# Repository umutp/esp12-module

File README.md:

# esp12-module
Simple Esp12 module design for home automation

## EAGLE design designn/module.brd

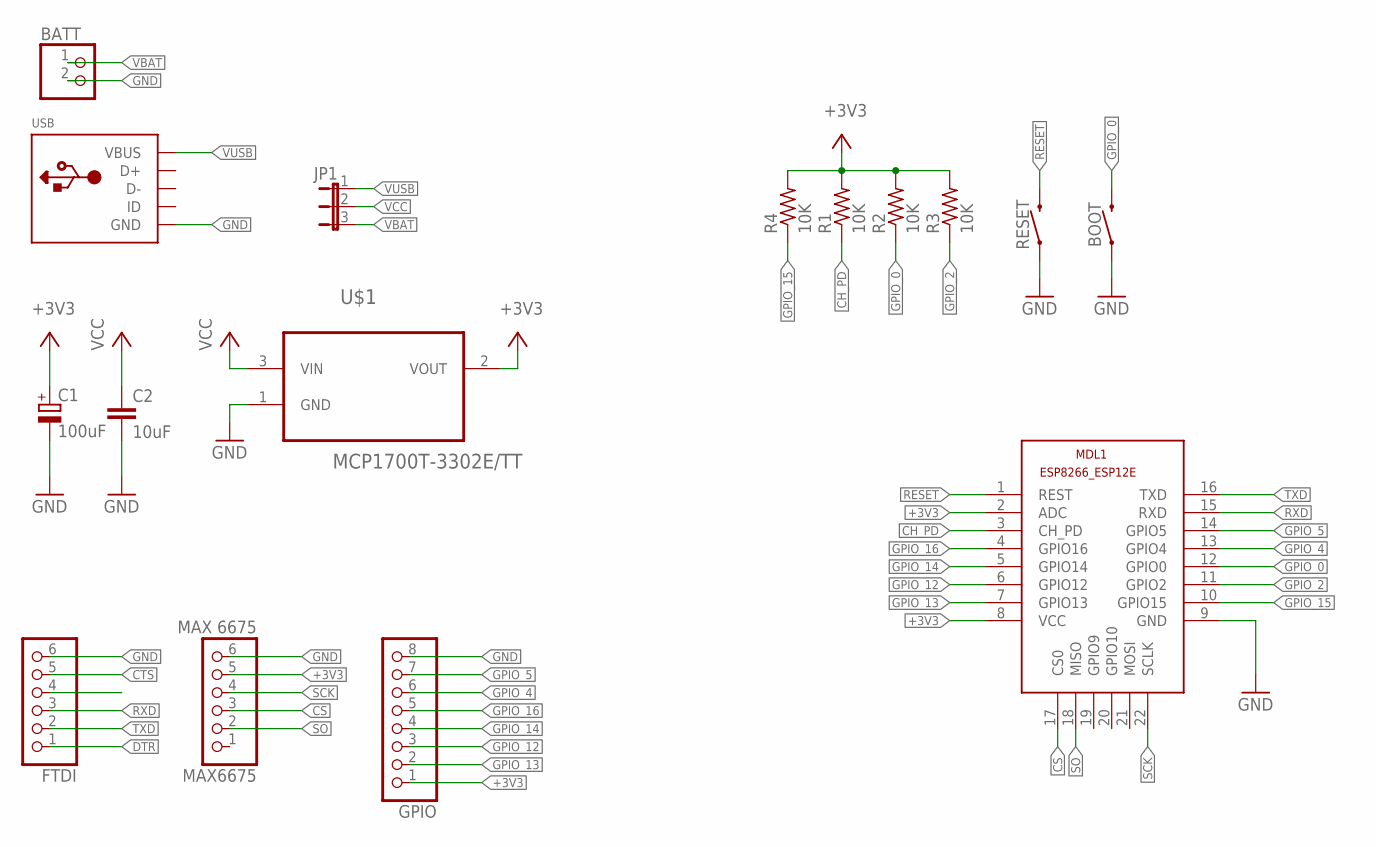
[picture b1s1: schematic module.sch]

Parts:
BATT: PINHD-1X2; 1X02
BOOT: gpio0; TACTILE_SWITCH_SMD_4.5MM
C1: 100uF; 085CS_1AR
C2: 10uF; C1206K
FTDI: PINHD-1X6B; 1X06-BIG
GPIO: PINHD-1X8BIG; 1X08-BIG
JP1: JP2E; JP2
MAX6675: MAX 6675; 1X06-BIG
MDL1: ESP8266-12EESP8266-ESP12E; ESP8266-ESP12E
R1, R2, R3, R4: 10K; M0805
RESET: reset; TACTILE_SWITCH_SMD_4.5MM
U$1: MCP1700T-3302E/TT; SOT95P237X112-3N
USB: USBMICRO_20329; 4UCONN_20329

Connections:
+3V3: C1.+, GPIO.1, MAX6675.5, MDL1.2 (ADC), MDL1.8 (VCC), R1.2, R2.2, R3.2, R4.2, U$1.2 (VOUT)
CH_PD: MDL1.3 (CH_PD), R1.1
CS: MAX6675.3, MDL1.17 (CS0)
CTS: FTDI.5
DTR: FTDI.1
GND: BATT.2, BOOT.2 (1), BOOT.3 (1), C1.-, C2.2, FTDI.6, GPIO.8, MAX6675.6, MDL1.9 (GND), RESET.2 (1), RESET.3 (1), U$1.1 (GND), USB.BASE@1 (GND), USB.BASE@2 (GND), USB.GND, USB.SPRT@1 (GND), USB.SPRT@2 (GND), USB.SPRT@3 (GND), USB.SPRT@4 (GND)
GPIO_0: BOOT.1 (2), BOOT.4 (2), MDL1.12 (GPIO0), R2.1
GPIO_2: MDL1.11 (GPIO2), R3.1
GPIO_4: GPIO.6, MDL1.13 (GPIO4)
GPIO_5: GPIO.7, MDL1.14 (GPIO5)
GPIO_12: GPIO.3, MDL1.6 (GPIO12)
GPIO_13: GPIO.2, MDL1.7 (GPIO13)
GPIO_14: GPIO.4, MDL1.5 (GPIO14)
GPIO_15: MDL1.10 (GPIO15), R4.1
GPIO_16: GPIO.5, MDL1.4 (GPIO16)
RESET: MDL1.1 (REST), RESET.1 (2), RESET.4 (2)
RXD: FTDI.3, MDL1.15 (RXD)
SCK: MAX6675.4, MDL1.22 (SCLK)
SO: MAX6675.2, MDL1.18 (MISO)
TXD: FTDI.2, MDL1.16 (TXD)
VBAT: BATT.1, JP1.3
VCC: C2.1, JP1.2, U$1.3 (VIN)
VUSB: JP1.1, USB.VBUS

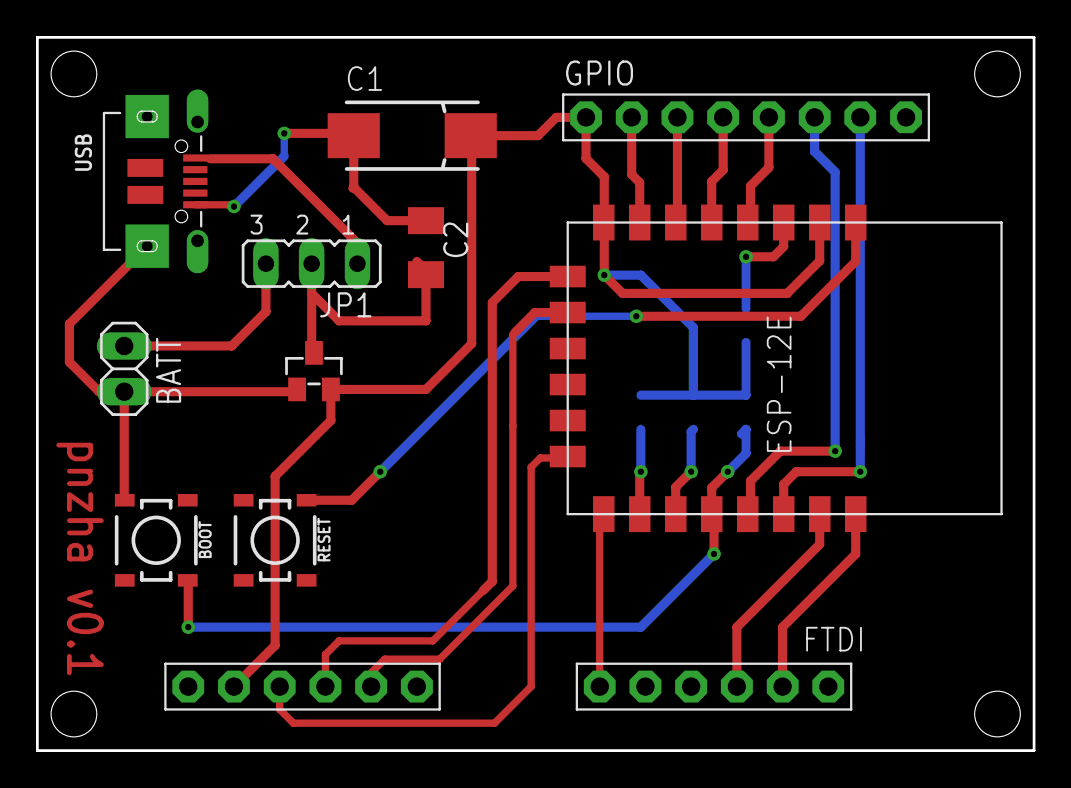
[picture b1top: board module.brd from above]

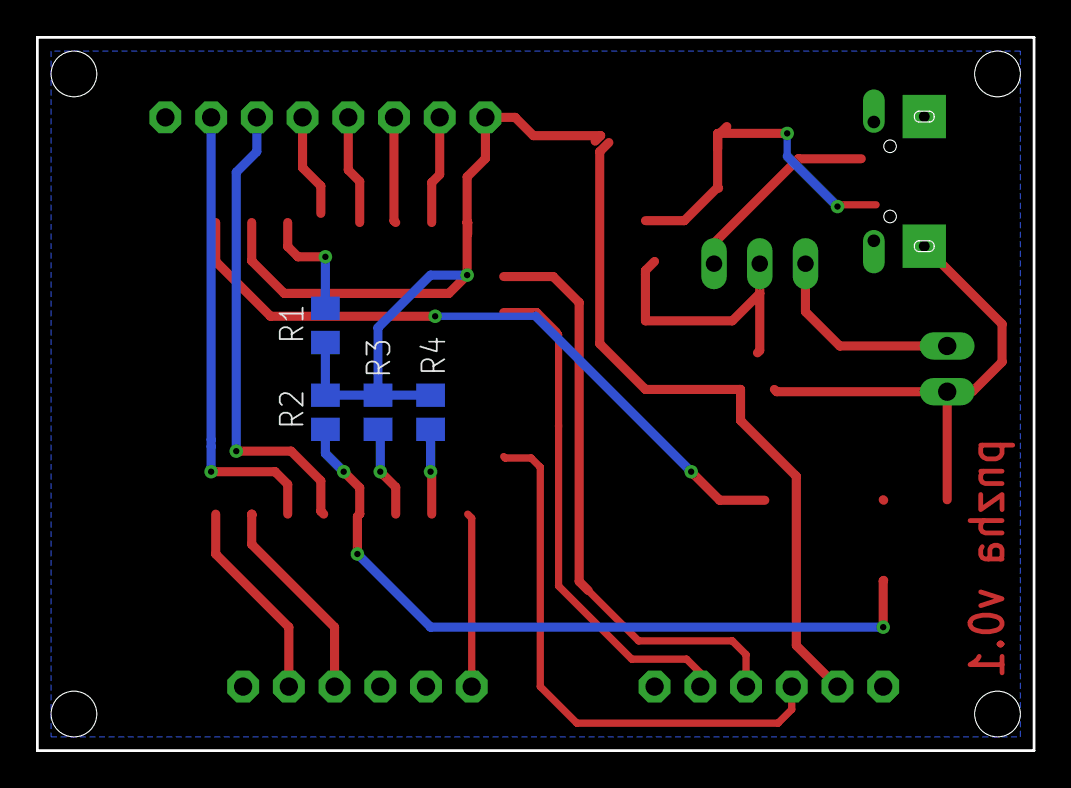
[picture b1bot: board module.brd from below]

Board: 2 copper layers, 55.4 x 39.6 mm, 16 parts (4 on the bottom side), 21 nets.

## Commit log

2020-04-27 initial commit.

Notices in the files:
parts and their libraries:
SparkFun-Switches: Licensing: Creative Commons ShareAlike 4.0 International - https://creativecommons.org/licenses/by-sa/4.0
